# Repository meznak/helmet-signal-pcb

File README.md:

# helmet-signal-pcb
Printed circuit boards for my wireless helmet signal ( https://github.com/meznak/helmet-signal )

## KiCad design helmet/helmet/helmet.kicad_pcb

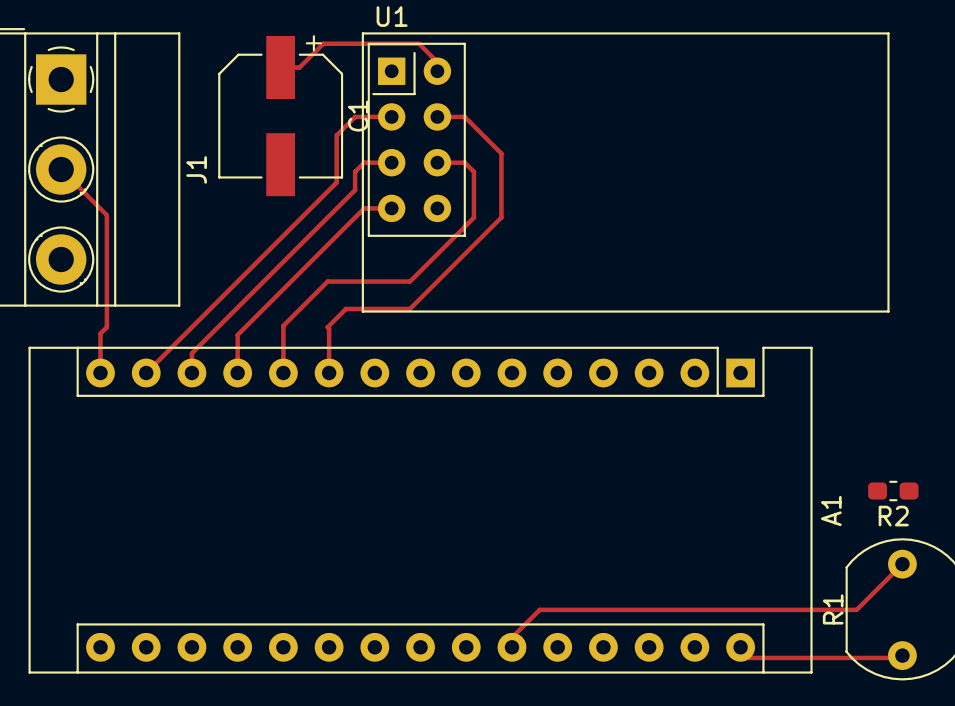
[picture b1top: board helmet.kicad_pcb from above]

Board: 2 copper layers, 6 parts (0 on the bottom side), 10 nets.

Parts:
A1: Arduino_Nano_v3.x; Arduino_Nano
C1: CP; CP_Elec_6.3x3
J1: Screw_Terminal_01x03; TerminalBlock_MetzConnect_Type011_RT05503HBWC_1x03_P5.00mm_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
R1: R_PHOTO; R_LDR_7x6mm_P5.1mm_Vertical
R2: 10k; R_0603_1608Metric_Pad1.05x0.95mm_HandSolder
U1: NRF24L01_Breakout; nRF24L01_Breakout

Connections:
+3V3: A1.17, C1.1, U1.2
+5V: A1.30, J1.3, R1.1
GND: A1.29, C1.2, J1.1, R2.2, U1.1
unnamed: A1.10, U1.4
unnamed: A1.11, U1.6
unnamed: A1.12, U1.7
unnamed: A1.13, U1.5
unnamed: A1.14, U1.3
unnamed: A1.15, J1.2
unnamed: A1.25, R1.2, R2.1

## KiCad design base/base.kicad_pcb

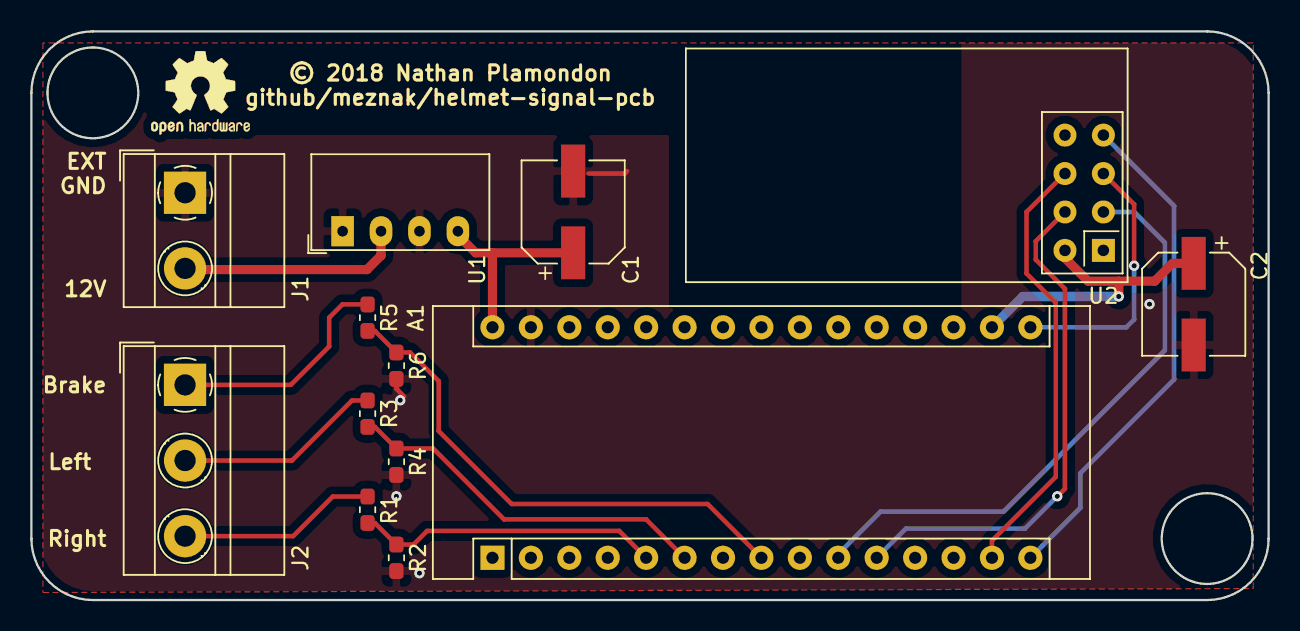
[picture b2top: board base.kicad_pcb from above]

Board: 2 copper layers, 81.8 x 37.6 mm, 13 parts (0 on the bottom side), 15 nets.

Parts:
A1: Arduino_Nano_v3.x; Arduino_Nano
C1, C2: 10uF; CP_Elec_6.3x3
J1: Screw_Terminal_01x02; TerminalBlock_MetzConnect_Type011_RT05502HBWC_1x02_P5.00mm_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
J2: Screw_Terminal_01x03; TerminalBlock_MetzConnect_Type011_RT05503HBWC_1x03_P5.00mm_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
R1, R3, R5: 120k; R_0603_1608Metric_Pad1.05x0.95mm_HandSolder
R2, R4, R6: 68k; R_0603_1608Metric_Pad1.05x0.95mm_HandSolder
U1: CRE1S1205SC; Converter_DCDC_muRata_CRE1xxxxxxSC_THT
U2: NRF24L01_Breakout; nRF24L01_Breakout

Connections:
+3V3: A1.17, C2.1, U2.2
+5V: A1.30, C1.1, U1.4
+12V: J1.2, U1.2
GND: A1.29, C1.2, C2.2, J1.1, R2.2, R4.2, R6.2, U1.1, U1.3, U2.1
unnamed: A1.5, R1.2, R2.1
unnamed: A1.6, R3.2, R4.1
unnamed: A1.8, R5.2, R6.1
unnamed: A1.10, U2.3
unnamed: A1.11, U2.4
unnamed: A1.14, U2.6
unnamed: A1.15, U2.7
unnamed: A1.16, U2.5
unnamed: J2.1, R5.1
unnamed: J2.2, R3.1
unnamed: J2.3, R1.1

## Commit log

2018-12-27 Lay out base schematic
2018-12-27 Update gitignore
2018-12-27 Base - Annotate and assign footprints
2018-12-27 Base - Start PCB layout
2018-12-27 Base - Lay out PCB
2018-12-30 Base - Combine GND nets
2018-12-30 Base - Clean up and EDC
2018-12-31 Helmet - Start schematic
2018-12-31 Helmet - Rearrange radio pins for better layout
2018-12-31 Helmet - Start PCB layout

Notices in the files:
base/base.kicad_pcb:
© 2018 Nathan Plamondon
